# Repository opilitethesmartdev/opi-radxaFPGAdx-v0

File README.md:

HAT board for the Radxa Zero 3e featuring an FPGA.

Author: opilitethesmartdev

FPGA Options:

* MAX II

  * Pros

    * readily available
    * altera = quartus = easy to use
    * supports Jam STAPL JTAG
    * KiCad support
  * Cons

    * Low resources
* Gowin GW1NR-LV9 (or maybe something even better)

  * Pros

    * More resources
    * HDMI and MIPI support (useful for stuff)
    * better price/performance
  * Cons

    * awful KiCad models
    * maybe (?) not so good documentation
    * idk about IP Cores

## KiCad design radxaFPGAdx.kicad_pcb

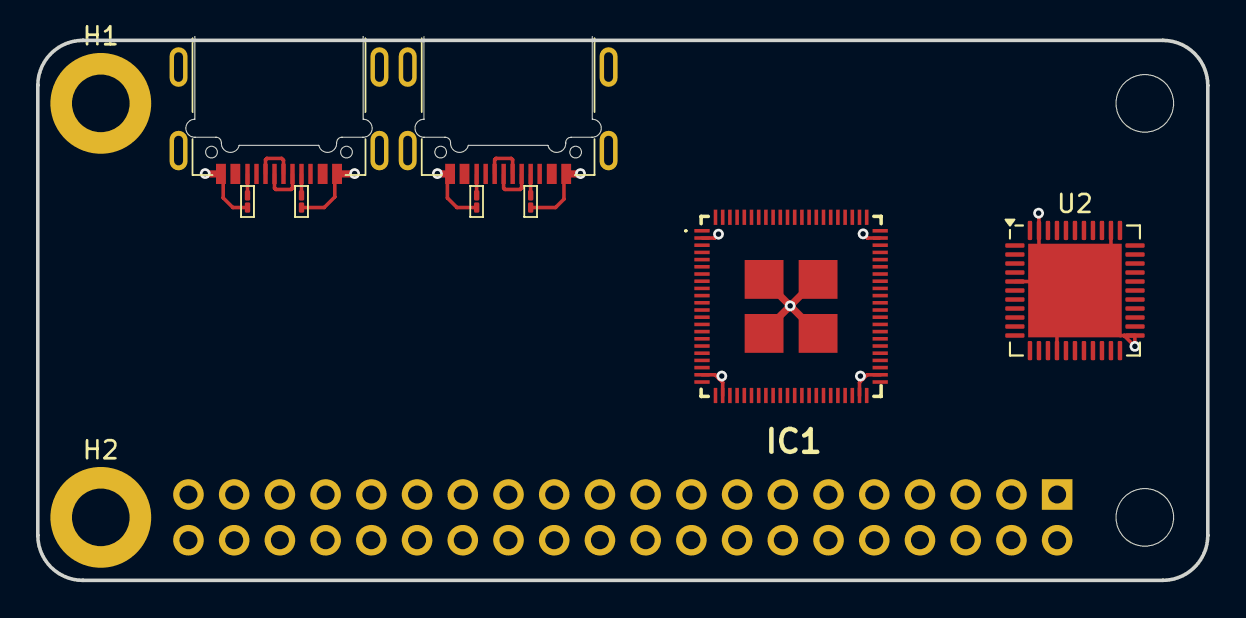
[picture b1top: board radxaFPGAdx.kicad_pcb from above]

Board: 2 copper layers, 65.0 x 30.0 mm, 11 parts (1 on the bottom side), 12 nets.

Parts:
H1, H2: MountingHole_Pad; MountingHole_3.2mm_M3_DIN965_Pad
IC1: GW1NR-LV9QN88C7_I6; GW1NRLV9QN88C7I6
J1: Conn_02x20_Odd_Even; PinSocket_2x20_P2.54mm_Vertical
J2: USB2_MEGA; TYPE-C-31-M-14
J3: USB2_FPGA; TYPE-C-31-M-14
R1, R2, R3, R4: 5.1k; R_01005_0402Metric_Pad0.57x0.30mm_HandSolder
U2: ATmega16U4-M; QFN-44-1EP_7x7mm_P0.5mm_EP5.2x5.2mm

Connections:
+5V: U2.2 (UVCC), U2.7 (VBUS), U2.14 (VCC), U2.24 (AVCC), U2.34 (VCC), U2.44 (AVCC)
/USB_Fm: J3.A7 (D-), J3.B7 (D-)
/USB_Fp: J3.A6 (D+), J3.B6 (D+)
/USB_Mm: J2.A7 (D-), J2.B7 (D-)
/USB_Mp: J2.A6 (D+), J2.B6 (D+)
GND: H1.1 (1_1), H2.1 (1_1), IC1.2 (VSS_1), IC1.21 (VSS_2), IC1.24 (VSS_3), IC1.43 (VSS_4), IC1.46 (VSS_5), IC1.65 (VSS_6), IC1.89 (GND_1), IC1.90 (GND_2), IC1.91 (GND_3), IC1.92 (GND_4), J1.6, J1.9, J1.14, J1.20, J1.25, J1.30, J1.34, J1.39, J2.A1 (GND), J2.A12 (GND), J2.B1 (GND), J2.B12 (GND), J3.A1 (GND), J3.A12 (GND), J3.B1 (GND), J3.B12 (GND), R1.2, R2.2, R3.2, R4.2, U2.5 (UGND), U2.15 (GND), U2.23 (GND), U2.35 (GND), U2.43 (GND), U2.45 (GND)
unnamed: J1.2, J1.4
unnamed: J2.A5 (CC1), R2.1
unnamed: J2.B5 (CC2), R1.1
unnamed: J3.A5 (CC1), R3.1
unnamed: J3.B5 (CC2), R4.1
VBUS: J2.A4 (VBUS), J2.A9 (VBUS), J2.B4 (VBUS), J2.B9 (VBUS), J3.A4 (VBUS), J3.A9 (VBUS), J3.B4 (VBUS), J3.B9 (VBUS)
